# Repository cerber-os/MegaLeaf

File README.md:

# MegaLeaf - next level RGB lightning

## Overview

## Microcontroller

## Userspace software

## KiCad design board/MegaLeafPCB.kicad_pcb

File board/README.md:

# MegaLeaf schematic and PCB

Hardware base of MegaLeaf project is a custom-designed and home-made PCB board, equipped with both STM32F4 and Esperif ESP32-C3 microcontrollers.

The main goal of this board was to support communication between LEDs strip and STM32F4 MCU via voltage level shifter. Furthermore, it connects MCU with both Esperif ESP32 Wifi module (for IoT cloud communication) and USB type C connector (used in old-school USB2.0-FS mode). Finally, there's a 3.3V linear stabilizer powered from the LEDs power supply and USB ESD protection.

## Schematic preview

**Note**: Full schematic as PDF document is available [here](renders/MegaLeafPCB.pdf).

## PCB views

The design of PCB has been stricly adapted for the process of making home-made DIY PCB board. That's why vias are huge (1.2mm hole diameter) and limited to the very minimum (as every single one of them has to be drilled manually), copper tracks are extra spaced when possible to prevent problems during itching process and all components are far from each other to ease soldering on board without soldermask.

But since, there aren't any very high frequency signals (48MHz from USB2.0 is the fastest line here), all of the above flaws should not affect final performance and stability of this board.

| Front | Back |
| -- | -- |
|  |  |

## Sources

Links to some useful resources used during board development:

1. Getting started with STM32F4 hardware development - [AN4488](https://www.st.com/resource/en/application_note/dm00115714-getting-started-with-stm32f4xxxx-mcu-hardware-development-stmicroelectronics.pdf)

2. Esperif hardware reference - [docs.esperif.com](https://docs.espressif.com/projects/esp-idf/en/latest/esp32c3/hw-reference/index.html)

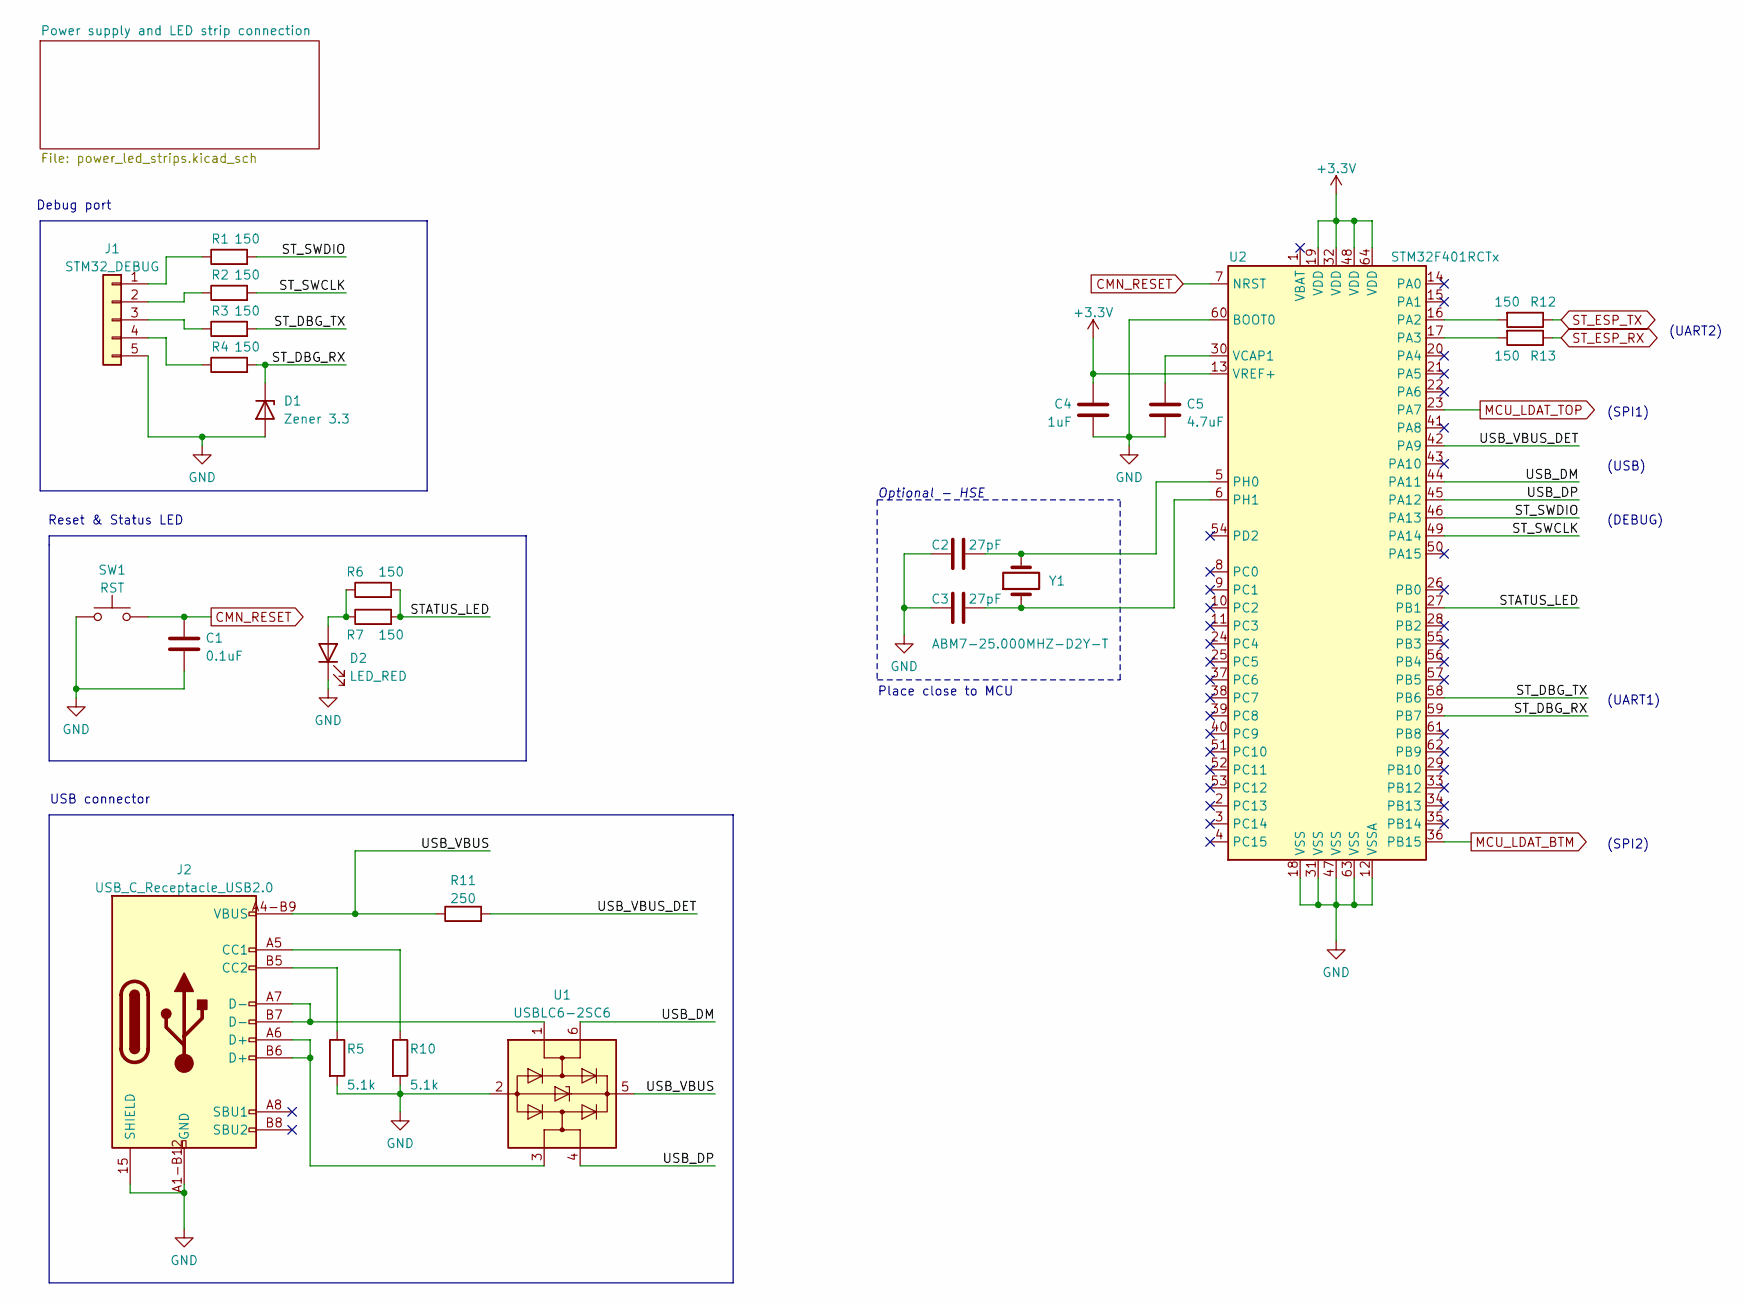
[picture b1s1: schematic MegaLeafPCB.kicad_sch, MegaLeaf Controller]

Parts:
C1: 0.1uF; C_0805_2012Metric_Pad1.18x1.45mm_HandSolder
C2, C3: 27pF; C_0603_1608Metric_Pad1.08x0.95mm_HandSolder
C4: 1uF; C_0805_2012Metric_Pad1.18x1.45mm_HandSolder
C5: 4.7uF; C_0805_2012Metric_Pad1.18x1.45mm_HandSolder
D1: Zener 3.3; SOT-23_Handsoldering
D2: LED_RED; D_0805_2012Metric_Pad1.15x1.40mm_HandSolder
J1: STM32_DEBUG; PinHeader_1x05_P2.54mm_Vertical_SMD_Pin1Left
J2: USB_C_Receptacle_USB2.0; USB4110-GF-A
R1, R2, R3, R4, R6, R7, R12, R13: 150; R_0805_2012Metric_Pad1.20x1.40mm_HandSolder
R5, R10: 5.1k; R_0805_2012Metric_Pad1.20x1.40mm_HandSolder
R11: 250; R_0805_2012Metric_Pad1.20x1.40mm_HandSolder
SW1: RST; SW_SPST_B3S-1000
U1: USBLC6-2SC6; SOT-23-6
U2: STM32F401RCTx; LQFP-64_10x10mm_P0.5mm
Y1: ABM7-25.000MHZ-D2Y-T; Crystal_SMD_Abracon_ABM7-2Pin_6.0x3.5mm

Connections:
+3.3V: C4.2, U2.13 (VREF+), U2.19 (VDD), U2.32 (VDD), U2.48 (VDD), U2.64 (VDD); also elsewhere on the board
/STATUS_LED: R6.2, R7.2, U2.27 (PB1)
/ST_DBG_RX: D1.1 (K), R4.2, U2.59 (PB7)
/ST_DBG_TX: R3.2, U2.58 (PB6)
/ST_SWCLK: R2.2, U2.49 (PA14)
/ST_SWDIO: R1.2, U2.46 (PA13)
/USB_DM: U1.6 (I/O1), U2.44 (PA11)
/USB_DP: U1.4 (I/O2), U2.45 (PA12)
/USB_VBUS: J2.A4-B9 (VBUS), J2.A9-B4 (VBUS), R11.1, U1.5 (VBUS)
/USB_VBUS_DET: R11.2, U2.42 (PA9)
CMN_RESET: C1.1, SW1.2, U2.7 (NRST); also elsewhere on the board
GND: C1.2, C2.1, C3.1, C4.1, C5.2, D1.2 (A), D2.1 (K), J1.5, J2.15 (SHIELD), J2.16 (SHIELD), J2.17 (SHIELD), J2.18 (SHIELD), J2.A1-B12 (GND), J2.A12-B1 (GND), R5.2, R10.2, SW1.1, U1.2 (GND), U2.12 (VSSA), U2.18 (VSS), U2.31 (VSS), U2.47 (VSS), U2.60 (BOOT0), U2.63 (VSS); also elsewhere on the board
MCU_LDAT_BTM: U2.36 (PB15); also elsewhere on the board
MCU_LDAT_TOP: U2.23 (PA7); also elsewhere on the board
unnamed: C2.2, U2.5 (PH0), Y1.2
unnamed: C3.2, U2.6 (PH1), Y1.1
unnamed: C5.1, U2.30 (VCAP1)
unnamed: D2.2 (A), R6.1, R7.1
unnamed: J1.1, R1.1
unnamed: J1.2, R2.1
unnamed: J1.3, R3.1
unnamed: J1.4, R4.1
unnamed: J2.A5 (CC1), R10.1
unnamed: J2.A6 (D+), J2.B6 (D+), U1.3 (I/O2)
unnamed: J2.A7 (D-), J2.B7 (D-), U1.1 (I/O1)
unnamed: J2.B5 (CC2), R5.1
unnamed: R12.2, U2.16 (PA2)
unnamed: R13.2, U2.17 (PA3)
ST_ESP_RX: R13.1; also elsewhere on the board
ST_ESP_TX: R12.1; also elsewhere on the board

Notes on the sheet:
(UART2)
Optional - HSE
(SPI2)
Reset & Status LED
(UART1)
Debug port
(SPI1)
(USB)
(DEBUG)
Place close to MCU
USB connector

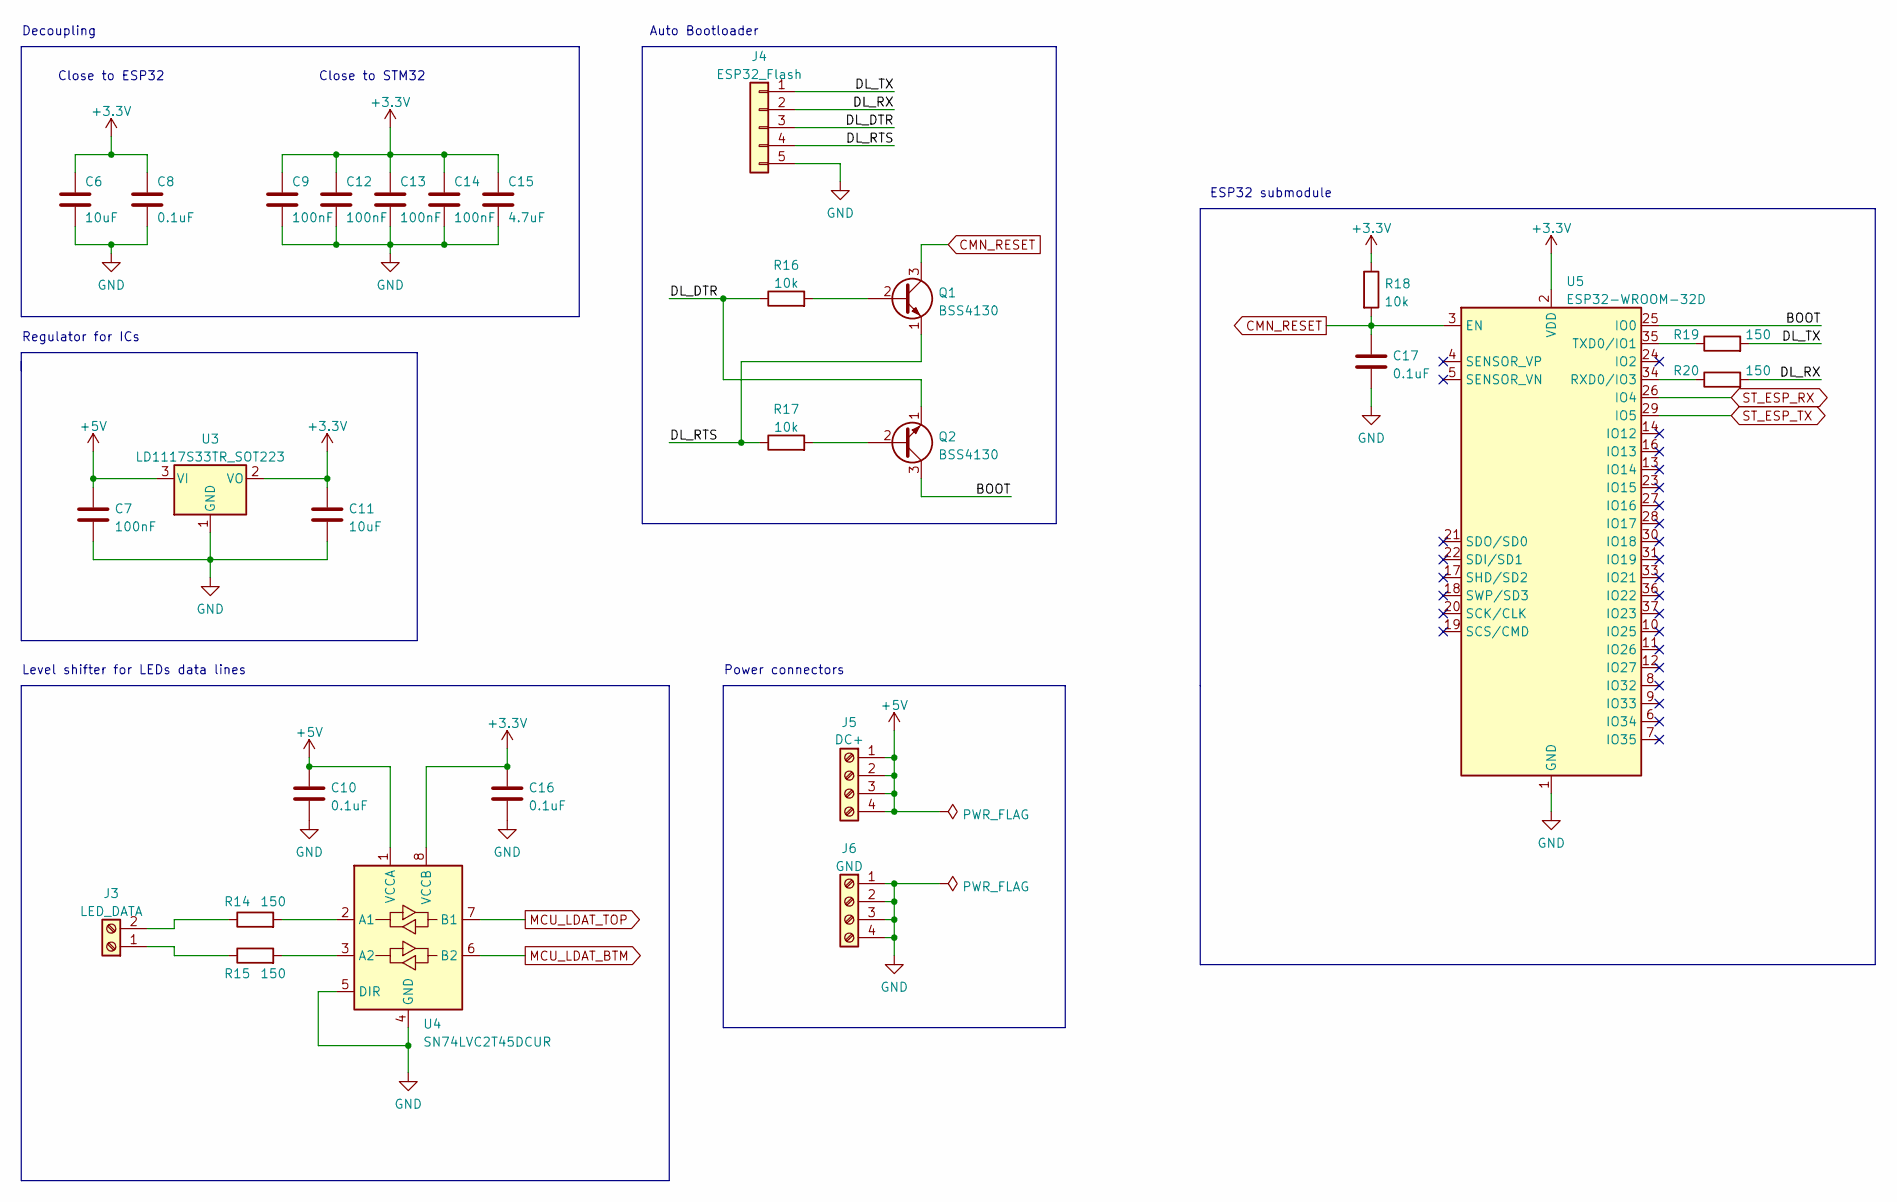
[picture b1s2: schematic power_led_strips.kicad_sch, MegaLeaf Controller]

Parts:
C6, C11: 10uF; C_0805_2012Metric_Pad1.18x1.45mm_HandSolder
C7, C9, C12, C13, C14: 100nF; C_0805_2012Metric_Pad1.18x1.45mm_HandSolder
C8, C10, C16, C17: 0.1uF; C_0805_2012Metric_Pad1.18x1.45mm_HandSolder
C15: 4.7uF; C_0805_2012Metric_Pad1.18x1.45mm_HandSolder
J3: LED_DATA; TerminalBlock_Phoenix_MKDS-1,5-2_1x02_P5.00mm_Horizontal
J4: ESP32_Flash; PinHeader_1x05_P2.54mm_Vertical_SMD_Pin1Left
J5: DC+; MC000020
J6: GND; MC000020
Q1, Q2: BSS4130; SOT-23
R14, R15, R19, R20: 150; R_0805_2012Metric_Pad1.20x1.40mm_HandSolder
R16, R17, R18: 10k; R_0805_2012Metric_Pad1.20x1.40mm_HandSolder
U3: LD1117S33TR_SOT223; SOT-223-3_TabPin2
U4: SN74LVC2T45DCUR; VSSOP-8_2.4x2.1mm_P0.5mm
U5: ESP32-WROOM-32D; ESP32-WROOM-32

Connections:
+3.3V: C6.1, C8.1, C9.1, C11.1, C12.1, C13.1, C14.1, C15.1, C16.1, R18.1, U3.2 (VO), U4.8 (VCCB), U5.2 (VDD); also elsewhere on the board
+5V: C7.1, C10.1, J5.1, J5.2, J5.3, J5.4, U3.3 (VI), U4.1 (VCCA)
/Power supply and LED strip connection/BOOT: Q2.3 (C), U5.25 (IO0)
/Power supply and LED strip connection/DL_DTR: J4.3, Q2.1 (E), R16.1
/Power supply and LED strip connection/DL_RTS: J4.4, Q1.1 (E), R17.1
/Power supply and LED strip connection/DL_RX: J4.2, R20.2
/Power supply and LED strip connection/DL_TX: J4.1, R19.2
CMN_RESET: C17.1, Q1.3 (C), R18.2, U5.3 (EN); also elsewhere on the board
GND: C6.2, C7.2, C8.2, C9.2, C10.2, C11.2, C12.2, C13.2, C14.2, C15.2, C16.2, C17.2, J4.5, J6.1, J6.2, J6.3, J6.4, U3.1 (GND), U4.4 (GND), U4.5 (DIR), U5.1 (GND), U5.15 (GND), U5.38 (GND), U5.39 (GND); also elsewhere on the board
MCU_LDAT_BTM: U4.6 (B2); also elsewhere on the board
MCU_LDAT_TOP: U4.7 (B1); also elsewhere on the board
unnamed: J3.1, R15.1
unnamed: J3.2, R14.1
unnamed: Q1.2 (B), R16.2
unnamed: Q2.2 (B), R17.2
unnamed: R14.2, U4.2 (A1)
unnamed: R15.2, U4.3 (A2)
unnamed: R19.1, U5.35 (TXD0/IO1)
unnamed: R20.1, U5.34 (RXD0/IO3)
ST_ESP_RX: U5.26 (IO4); also elsewhere on the board
ST_ESP_TX: U5.29 (IO5); also elsewhere on the board

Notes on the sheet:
Decoupling
ESP32 submodule
Regulator for ICs
Auto Bootloader
Power connectors
Close to STM32
Close to ESP32
Level shifter for LEDs data lines

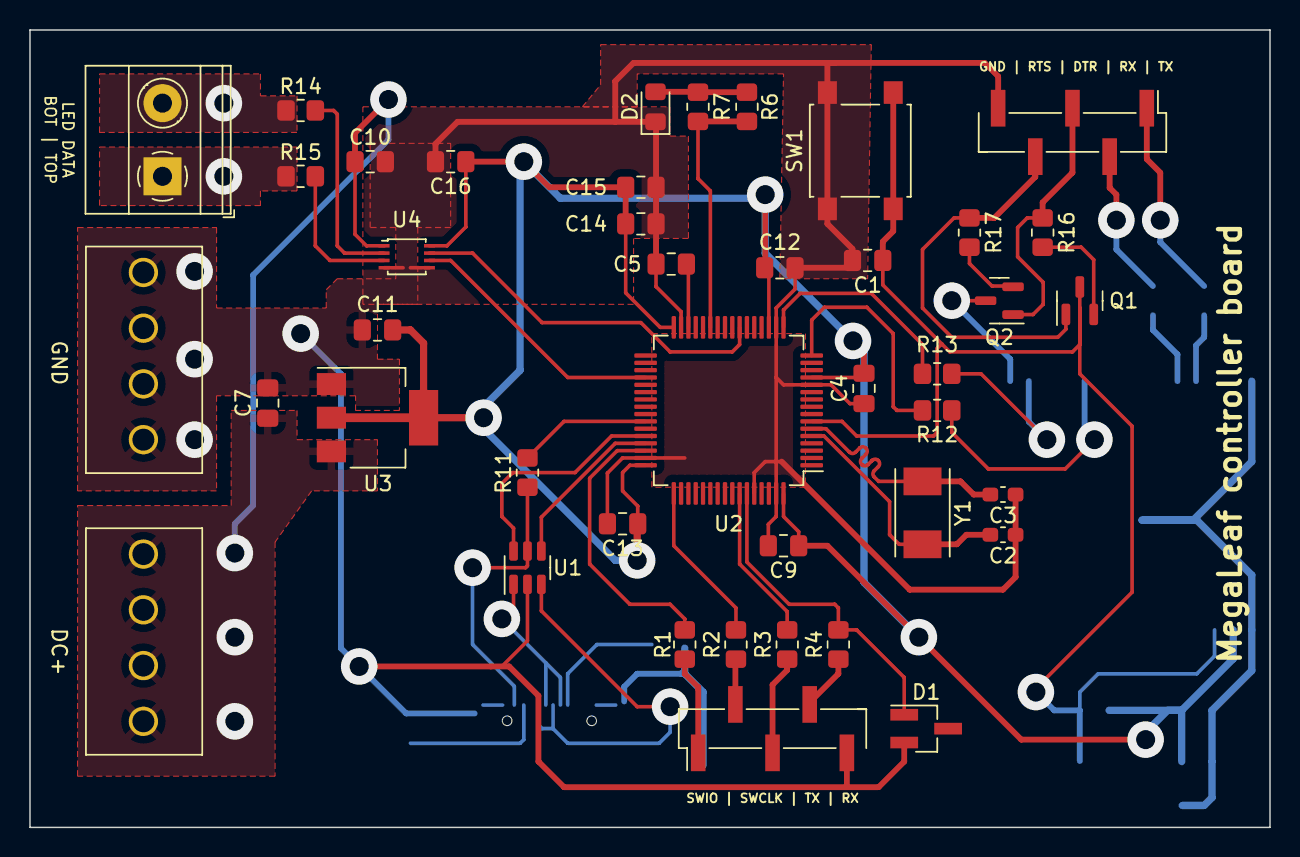
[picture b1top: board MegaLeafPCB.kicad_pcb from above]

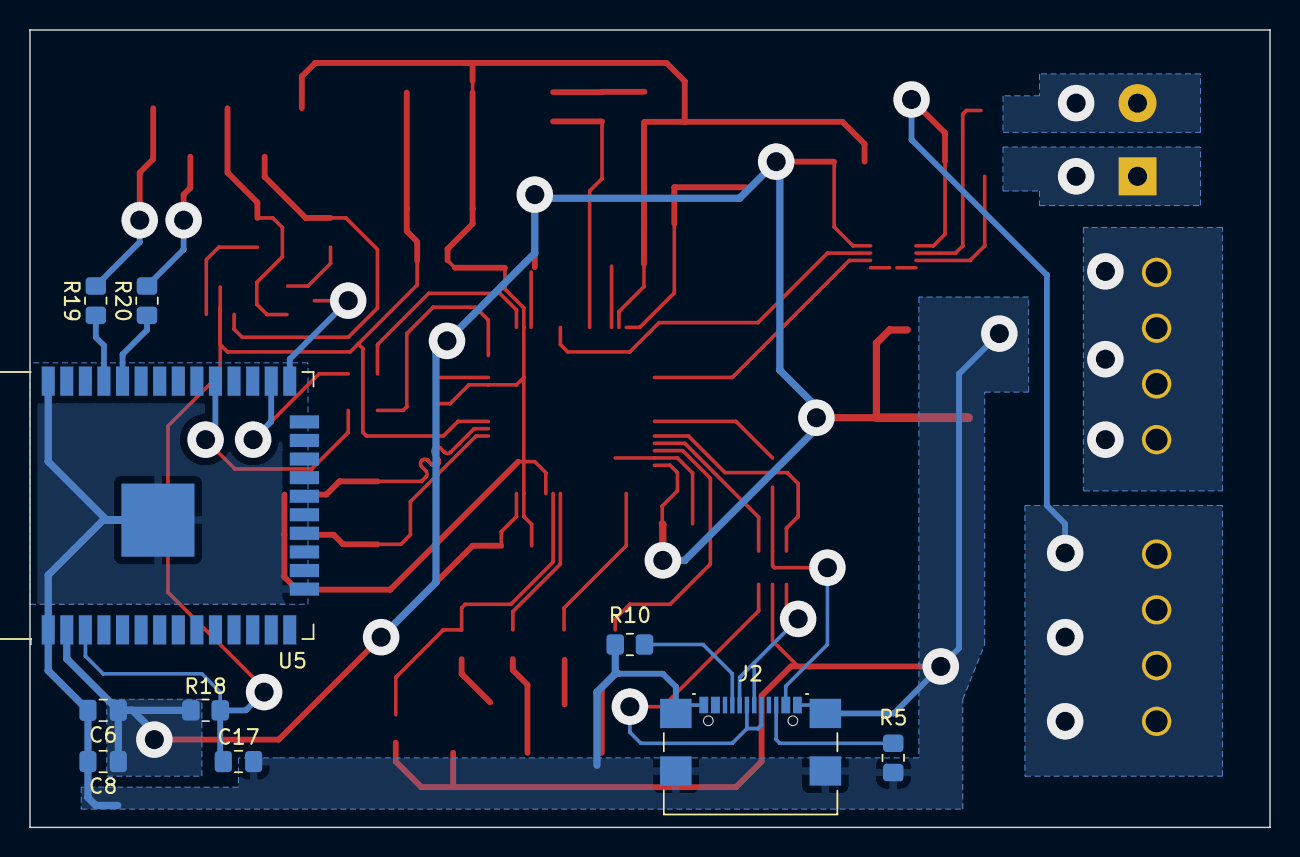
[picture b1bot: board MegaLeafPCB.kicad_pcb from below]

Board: 2 copper layers, 84.8 x 54.5 mm, 52 parts (10 on the bottom side), 44 nets.

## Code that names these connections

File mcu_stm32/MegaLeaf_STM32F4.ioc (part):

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Mcu.Name=STM32F401R(B-C)Tx
Mcu.Package=LQFP64
Mcu.UserName=STM32F401RCTx
PA11.Mode=Device_Only
PA11.Signal=USB_OTG_FS_DM
PA12.Mode=Device_Only
PA12.Signal=USB_OTG_FS_DP
PA13.Mode=Serial_Wire
PA13.Signal=SYS_JTMS-SWDIO
PA14.Mode=Serial_Wire
PA14.Signal=SYS_JTCK-SWCLK
PA2.GPIOParameters=GPIO_Speed,GPIO_PuPd,GPIO_Label
PA2.GPIO_Label=ST_ESP_TX
PA2.GPIO_PuPd=GPIO_PULLUP
PA2.GPIO_Speed=GPIO_SPEED_FREQ_MEDIUM
PA2.Mode=Asynchronous
PA2.Signal=USART2_TX
PA3.GPIOParameters=GPIO_Speed,GPIO_PuPd,GPIO_Label
PA3.GPIO_Label=ST_ESP_RX
PA3.GPIO_PuPd=GPIO_PULLUP
PA3.GPIO_Speed=GPIO_SPEED_FREQ_MEDIUM
PA3.Mode=Asynchronous
PA3.Signal=USART2_RX
PA5.GPIOParameters=GPIO_Speed
PA5.GPIO_Speed=GPIO_SPEED_FREQ_LOW
PA5.Mode=TX_Only_Simplex_Unidirect_Master
PA5.Signal=SPI1_SCK
PA7.GPIOParameters=GPIO_PuPd
PA7.GPIO_PuPd=GPIO_NOPULL
PA7.Mode=TX_Only_Simplex_Unidirect_Master
PA7.Signal=SPI1_MOSI
PA9.Mode=Activate_VBUS
PA9.Signal=USB_OTG_FS_VBUS
PB1.GPIOParameters=GPIO_PuPd,GPIO_Label
PB1.GPIO_Label=STATUS_LED
PB1.GPIO_PuPd=GPIO_PULLDOWN
PB1.Signal=GPIO_Output
PB10.GPIOParameters=GPIO_Speed
PB10.GPIO_Speed=GPIO_SPEED_FREQ_LOW
PB10.Mode=TX_Only_Simplex_Unidirect_Master
PB10.Signal=SPI2_SCK
PB15.GPIOParameters=GPIO_Speed,GPIO_PuPd,GPIO_Label
PB15.GPIO_Label=MCU_LDAT_BTM
PB15.GPIO_PuPd=GPIO_NOPULL
PB15.GPIO_Speed=GPIO_SPEED_FREQ_VERY_HIGH
PB15.Mode=TX_Only_Simplex_Unidirect_Master
PB15.Signal=SPI2_MOSI
PB6.GPIOParameters=GPIO_Speed,GPIO_PuPd,GPIO_Label
PB6.GPIO_Label=ST_DBG_TX
PB6.GPIO_PuPd=GPIO_PULLUP
PB6.GPIO_Speed=GPIO_SPEED_FREQ_MEDIUM
PB6.Mode=Asynchronous
PB6.Signal=USART1_TX
PB7.GPIOParameters=GPIO_Speed,GPIO_PuPd,GPIO_Label
PB7.GPIO_Label=ST_DBG_RX
PB7.GPIO_PuPd=GPIO_PULLUP
PB7.GPIO_Speed=GPIO_SPEED_FREQ_MEDIUM
PB7.Mode=Asynchronous
PB7.Signal=USART1_RX
PH0\ -\ OSC_IN.Mode=HSE-External-Oscillator
PH0\ -\ OSC_IN.Signal=RCC_OSC_IN
PH1\ -\ OSC_OUT.Mode=HSE-External-Oscillator
PH1\ -\ OSC_OUT.Signal=RCC_OSC_OUT
RCC.HSE_VALUE=25000000
RCC.SYSCLKFreq_VALUE=84000000
RCC.SYSCLKSource=RCC_SYSCLKSOURCE_PLLCLK
board=custom

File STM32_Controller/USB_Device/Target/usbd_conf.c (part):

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
    __HAL_RCC_GPIOA_CLK_ENABLE();
    /**USB GPIO Configuration
    PA11     ------> USB_DM
    PA12     ------> USB_DP
    */
    GPIO_InitStruct.Pin = GPIO_PIN_11|GPIO_PIN_12;
    GPIO_InitStruct.Mode = GPIO_MODE_AF_PP;
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    __HAL_RCC_USB_CLK_DISABLE();

    /**USB GPIO Configuration
    PA11     ------> USB_DM
    PA12     ------> USB_DP
    */
    HAL_GPIO_DeInit(GPIOA, GPIO_PIN_11|GPIO_PIN_12);

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
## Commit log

2022-06-13 Initial commit
    Add base version of userspace library
2022-06-13 Add .gitignore file
2022-06-13 Fix USB communication. Add support for remaining commands
2022-06-14 Add C bindings. Fix error handling
2022-06-14 Improve C bindings for MLFProtoLib
    Fix compiler warnings
2022-06-14 Add Python3 bindings to MLFProtoLib
2022-06-14 Add CMake config file
2022-06-14 [MCU] Upload controller project
2022-06-14 [Lib] Add symlink to protocol UAPI
2022-06-14 [MCU] Add USB related source code
2022-06-14 [MCU] Upload CMSIS and HAL libraries
2022-06-14 [Lib] Remove main function
2022-06-18 [Lib] Add support for Windows
2022-06-18 [Lib] Add README.md file with API examples
2022-06-23 [Lib] Fix communication errors and Windows support
2022-06-23 [MCU] Add support for custom colors command
    Update STM32CubeMX revision
2022-06-23 [MCU] Fix transmission errors caused by unexpected interrupts
2022-07-22 [Lib] Remove CRC checksum calculation
2022-07-22 [Lib] Add C API for retrieving error msg
2022-11-14 [MCU] Convert to STM32F4 microcontroller
2022-11-14 [Lib] Update UAPI. Fix exception handling
2022-11-14 [Lib] Fix includes in MLF library
2022-11-14 [Lib] Update examples in library README.md
2022-11-14 [MCU] Delete compiled files
2022-11-14 [SCH] Upload KiCad schematic files
2022-11-14 [SCH] Add README.md and docs
2022-11-14 [Lib] Rename library directory
2022-11-25 [ESP] Upload code for ESP32 board
2022-11-25 Update .gitignore file
2022-11-25 [Lib] Fix compilation issue on MSVC
2022-11-25 [Win] Update Windows app
    * Add NotifyIcon in tray bar for easier control
    * Support right-click menu on this icon
    * Allow process to close cmd window and enter background
    * Add cmdline arguments parsing
    * Improve error handling in Desktop Duplication API
2022-11-25 [Win] Add Windows app for controlling ambilight
2022-11-25 Add README.md template
2022-11-25 [MCU] Fix incorrect rounding of brightness
2022-11-25 [MCU] Fix progress bar effect
2022-11-25 [Lib] Add support for remaining MegaLeaf commands
2022-11-25 [MCU] Rename directories
2022-11-25 [Lib] Update README.md. Update Python code
2022-11-25 [Win] Add README.md
2022-11-25 [ESP] Add README.md for Esperif project
2022-11-25 Create License file
2023-01-05 [Board] Update README.md
2023-01-05 [Lib] Update README.md
2023-01-05 [Win] Update README.md
2023-05-24 [ESP] Fix state synchronization over USB
2023-05-24 [Win] Fix handling leds state from context menu
2023-08-14 Add st-device-sdk-c repository as submodule
2023-08-14 [ESP] Fix building project outside of st-device-sdk-c repo
    Improve CMakeLists.txt and other build files so that project can be
    built with idf.py without need to embed it into st-device-sdk-c
    repository
2023-08-15 [ESP] Update building instructions in README.md file
2023-08-17 [Win] Minor adjustements to README.md file

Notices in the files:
STM32_Controller/USB_Device/Target/usbd_conf.c:
© Copyright (c) 2022 STMicroelectronics.
All rights reserved.
This software component is licensed by ST under Ultimate Liberty license
parts and their libraries:
Copyright 2021 Accelerated Designs. All rights reserved.
